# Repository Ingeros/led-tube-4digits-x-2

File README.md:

# led-tube-7-segment-8-digits
KICAD PCB design  for 8 digits of 7-segment display driver by MAX7215

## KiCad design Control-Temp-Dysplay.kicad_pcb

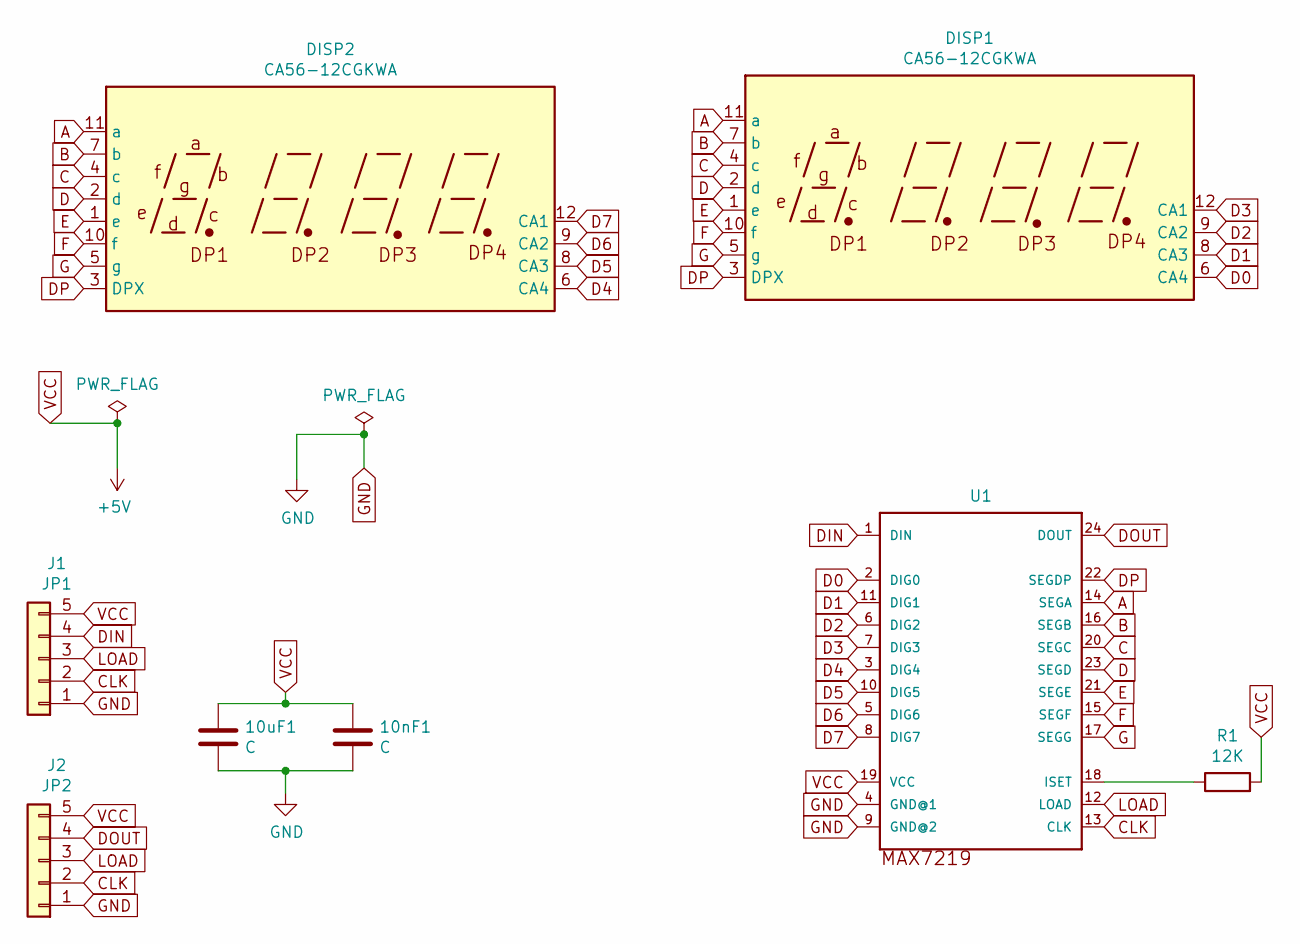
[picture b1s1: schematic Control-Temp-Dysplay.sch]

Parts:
10nF1: C; C_Axial_L3.8mm_D2.6mm_P7.50mm_Horizontal
10uF1: C; CP_Radial_D4.0mm_P1.50mm
DISP1, DISP2: CA56-12CGKWA
J1: JP1; PinSocket_1x05_P2.54mm_Vertical
J2: JP2; PinSocket_1x05_P2.54mm_Vertical
R1: 12K; R_Axial_DIN0309_L9.0mm_D3.2mm_P15.24mm_Horizontal
U1: MAX7219; DIP-24_W7.62mm_Socket

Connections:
A: DISP1.11 (a), DISP2.11 (a), U1.14 (SEGA)
B: DISP1.7 (b), DISP2.7 (b), U1.16 (SEGB)
C: DISP1.4 (c), DISP2.4 (c), U1.20 (SEGC)
CLK: J1.2, J2.2, U1.13 (CLK)
D: DISP1.2 (d), DISP2.2 (d), U1.23 (SEGD)
D0: DISP1.6 (CA4), U1.2 (DIG0)
D1: DISP1.8 (CA3), U1.11 (DIG1)
D2: DISP1.9 (CA2), U1.6 (DIG2)
D3: DISP1.12 (CA1), U1.7 (DIG3)
D4: DISP2.6 (CA4), U1.3 (DIG4)
D5: DISP2.8 (CA3), U1.10 (DIG5)
D6: DISP2.9 (CA2), U1.5 (DIG6)
D7: DISP2.12 (CA1), U1.8 (DIG7)
DIN: J1.4, U1.1 (DIN)
DOUT: J2.4, U1.24 (DOUT)
DP: DISP1.3 (DPX), DISP2.3 (DPX), U1.22 (SEGDP)
E: DISP1.1 (e), DISP2.1 (e), U1.21 (SEGE)
F: DISP1.10 (f), DISP2.10 (f), U1.15 (SEGF)
G: DISP1.5 (g), DISP2.5 (g), U1.17 (SEGG)
GND: 10nF1.2, 10uF1.2, J1.1, J2.1, U1.4 (GND@1), U1.9 (GND@2)
LOAD: J1.3, J2.3, U1.12 (LOAD)
unnamed: R1.1, U1.18 (ISET)
VCC: 10nF1.1, 10uF1.1, J1.5, J2.5, R1.2, U1.19 (VCC)

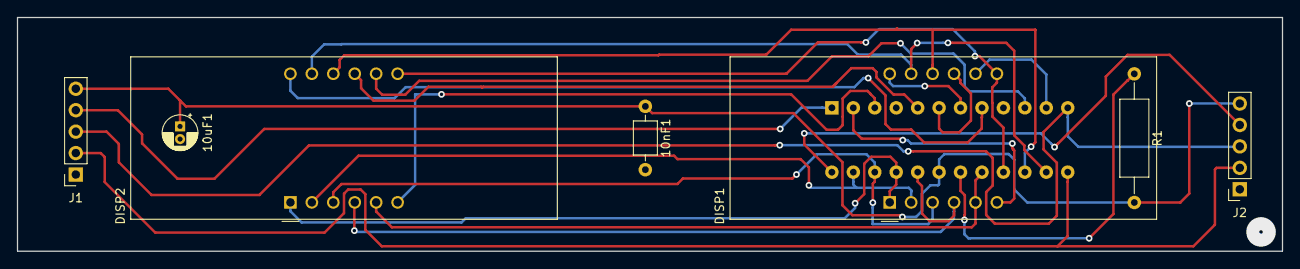
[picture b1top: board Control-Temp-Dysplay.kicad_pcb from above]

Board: 2 copper layers, 149.9 x 27.7 mm, 8 parts (1 on the bottom side), 23 nets.

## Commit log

2018-12-18 datasheet
